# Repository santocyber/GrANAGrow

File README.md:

# GrANAGrow
Telemetria de monitoramento de Grows

https://santocyber.helioho.st/granagw/

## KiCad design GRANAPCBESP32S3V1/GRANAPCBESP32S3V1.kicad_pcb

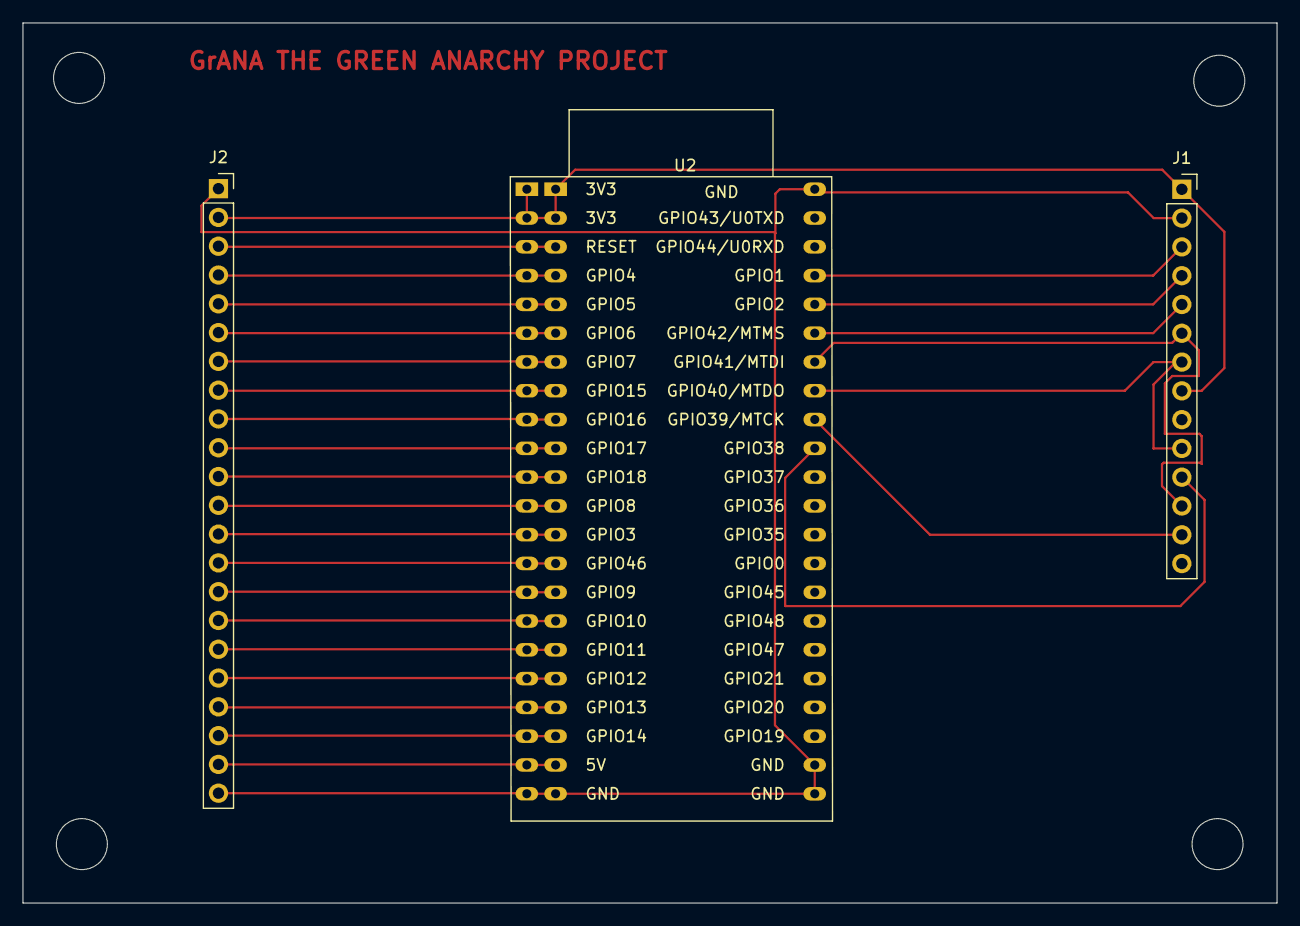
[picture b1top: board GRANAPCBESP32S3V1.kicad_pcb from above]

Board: 2 copper layers, 110.7 x 77.7 mm, 7 parts (0 on the bottom side), 28 nets.

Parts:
J1: Conn_01x14_Socket; PinSocket_1x14_P2.54mm_Vertical
J2: Conn_01x22_Pin; PinSocket_1x22_P2.54mm_Vertical
REF1, REF2, REF3, REF4: MountingHole_4.5mm
U2: ESP32-S3-DevKitC

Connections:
unnamed: J1.1, J1.8, J2.2, U2.1 (3V3), U2.2 (3V3)
unnamed: J1.2, J2.1, J2.22, U2.22 (GND), U2.23 (GND), U2.24 (GND), U2.44 (GND)
unnamed: J1.3, U2.41 (GPIO1/ADC1_CH0)
unnamed: J1.4, U2.40 (GPIO2/ADC1_CH1)
unnamed: J1.5, U2.39 (GPIO42/MTMS)
unnamed: J1.7, J1.10, U2.37 (GPIO40/MTDO)
unnamed: J1.11, U2.35 (GPIO38)
unnamed: J1.6, J1.12, U2.38 (GPIO41/MTDI)
unnamed: J1.13, U2.36 (GPIO39/MTCK)
unnamed: J2.3, U2.3 (CHIP_PU)
unnamed: J2.4, U2.4 (GPIO4/ADC1_CH3)
unnamed: J2.5, U2.5 (GPIO5/ADC1_CH4)
unnamed: J2.6, U2.6 (GPIO6/ADC1_CH5)
unnamed: J2.7, U2.7 (GPIO7/ADC1_CH6)
unnamed: J2.8, U2.8 (GPIO15/ADC2_CH4/32K_P)
unnamed: J2.9, U2.9 (GPIO16/ADC2_CH5/32K_N)
unnamed: J2.10, U2.10 (GPIO17/ADC2_CH6)
unnamed: J2.11, U2.11 (GPIO18/ADC2_CH7)
unnamed: J2.12, U2.12 (GPIO8/ADC1_CH7)
unnamed: J2.13, U2.13 (GPIO3/ADC1_CH2)
unnamed: J2.14, U2.14 (GPIO46)
unnamed: J2.15, U2.15 (GPIO9/ADC1_CH8)
unnamed: J2.16, U2.16 (GPIO10/ADC1_CH9)
unnamed: J2.17, U2.17 (GPIO11/ADC2_CH0)
unnamed: J2.18, U2.18 (GPIO12/ADC2_CH1)
unnamed: J2.19, U2.19 (GPIO13/ADC2_CH2)
unnamed: J2.20, U2.20 (GPIO14/ADC2_CH3)
unnamed: J2.21, U2.21 (5V)

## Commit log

2023-12-01 adicionei o committest
2023-12-01 add INO code
2023-12-01 add php code
2023-12-01 mudanca indexphp
2023-12-01 mudanca php
2024-02-12 Rename APK.dart to lib/main.dart
